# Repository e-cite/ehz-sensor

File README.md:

# EHZ Sensor
## Aufbau und Funktionsweise
Schaltpläne, PCB und Software für ein 2-Kanal Smart-Meter (EHZ EDL-21) Auswerte-Tool für ESP32
und Arduino UNO.

Mit einem Infrarot (IR) Schreib-Lesekopf können die IR-Signale des Smart-Meters eingelesen werden.
Eine Transistorstufe bereitet die Signale auf und invertiert diese, um als RX-Signal vom
Controller verarbeitet zu werden. Der Controller parsed die empfangenen Daten und verarbeitet
diese weiter.

## Software
Die Schaltpläne sind mit KiCAD (https://www.kicad.org/) erstellt.

Als IDE kommt die Arduino IDE (https://www.arduino.cc/en/software/) zum Einsatz.

## Hardware
Die Abmessungen des IR Schreib-Lesekopfes sind aus folgendem Projekt zu entnehmen:
[GitHub/e-cite/arduino-ehz-diag](https://github.com/e-cite/arduino-ehz-diag)

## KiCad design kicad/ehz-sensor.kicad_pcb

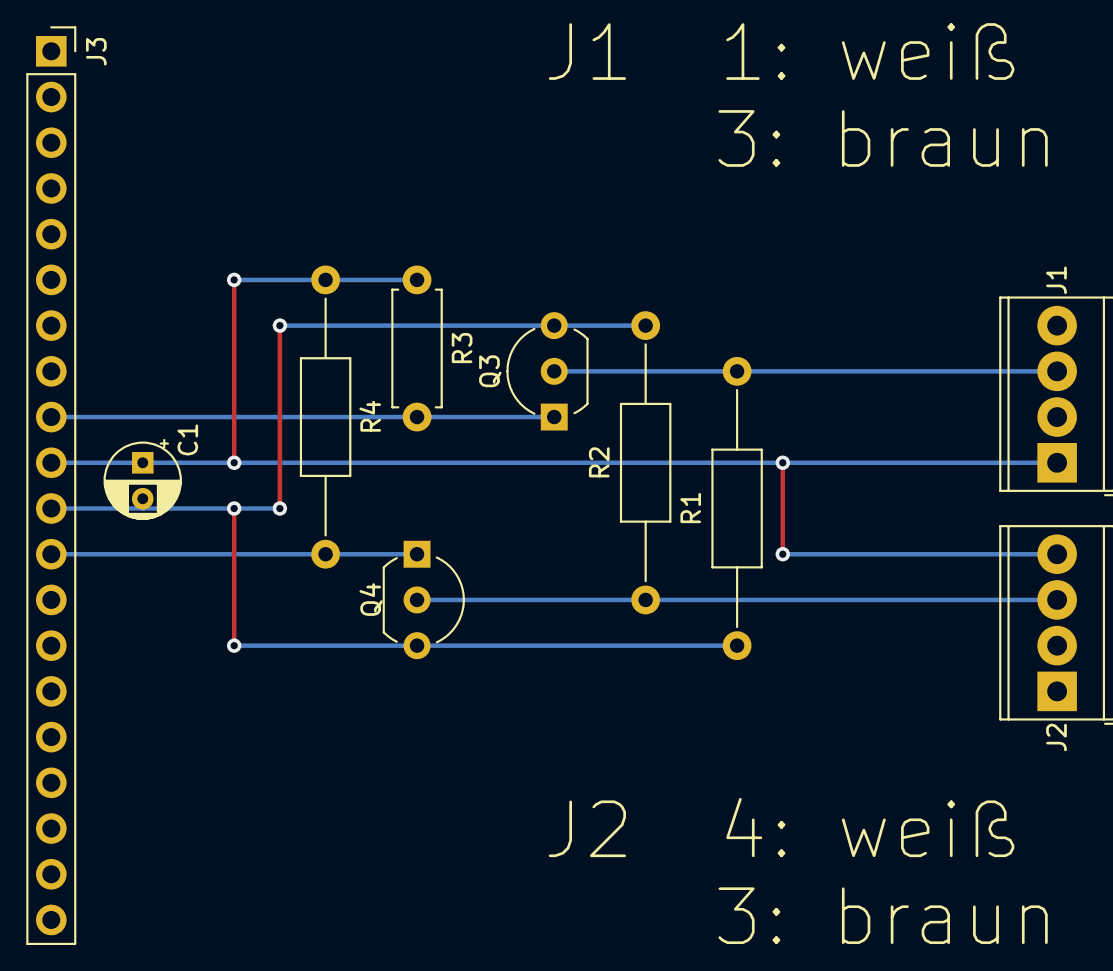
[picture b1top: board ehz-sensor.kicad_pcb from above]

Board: 2 copper layers, 10 parts (0 on the bottom side), 6 nets.

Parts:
C1: 1µ; CP_Radial_D4.0mm_P2.00mm
J1, J2: Screw-Terminal; TerminalBlock_Phoenix_MPT-0,5-4-2.54_1x04_P2.54mm_Horizontal
J3: Buchsenleiste 20x; PinSocket_1x20_P2.54mm_Vertical
Q3, Q4: BC548; TO-92_Inline_Wide
R1, R2, R4: 10k; R_Axial_DIN0207_L6.3mm_D2.5mm_P15.24mm_Horizontal
R3: 10k; R_Axial_DIN0207_L6.3mm_D2.5mm_P7.62mm_Horizontal

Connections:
+5V: C1.1, J1.1, J2.4, J3.10, R3.1, R4.1
/RXD1: J3.9, Q3.1, R3.2
/RXD2: J3.12, Q4.1, R4.2
GND: C1.2, J3.11, Q3.3, Q4.3, R1.2, R2.2
unnamed: J1.3, Q3.2, R1.1
unnamed: J2.3, Q4.2, R2.1

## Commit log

2022-01-01 Initiale Version.
